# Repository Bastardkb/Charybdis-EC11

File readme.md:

# Charybdis EC11 PCB

EC11 PCB to be used in place of the trackball in the Charybdis keyboard.

`REV 1.2` is tested and working.

## EC11 Encoder
R1 and R2 pins are used for the encoder rotation pulses, these should be connected to unused pins on the microcontroller. The MOSI/MISO/SCLK/CS will be the most convenient - any two of these can be used.

For normal configuration of the pushbutton function with the Charybdis:
 - Bridge the 2 unmarked pads on the solder jumper
 - install a SOD-123 diode in the marked footprint
 - connect Col to a column and BTN to a row that corresponds with the missing thumb key matrix position

If your keyboard uses direct pin you will need to bridge the middle pad on the solder jumper with the marked pad. BTN should then be connected to a free GPIO pin on your microcontroller.

## LEDs
LEDs are optional. If not being used, VCC, GND, DIN, and DO can be ignored.

Otherwise:
- Install the capacitor and resistor on the marked footprints
- VCC and GND can be connected to wherever is the most convenient
- DIN and DO should be connected as part of the existing LED chain on the half - the suggested way to do this is to connect the DO from the PCB plate to the EC11 adapter DIN (instead of the thumb cluster), and the thumb cluster pcb DIN to the EC11 adapter DO

## Misc. Note
It should be possible to connect the adapter directly to the 6 pins of the trackball pin header on the shield for better aesthetics and modularity. However this would need custom matrix scanning code - to mix direct pin and switch matrix scanning, as well as a custom RGB LED driver to allow a second `RGB_DI` pin to be defined

## Parts you will need
### For every build

| Part name           | Amount | Format  |
| ------------------- | ------ | ------- |
| Diode, 1N4148       | 1      | SOD-123 |
| EC11 Rotary encoder | 1      |         |
| Rotary encoder PCB* | 1      |         |

*order the PCB using the latest *gerbers.zip from here: [Releases](https://github.com/Bastardkb/Charybdis-EC11/releases)

### Optional for LED functionality
| Part name        | Amount per board | Format | Value  |
| ---------------- | ---------------- | ------ | ------ |
| SK6812-MINI-E    | 12               |        |        |
| Capacitor        | 1                | 1206   | 1uF    |
| Resistor         | 1                | 1206   | 330ohm |

## Knob
The knob work on the 20mm tall and 6mm diameter knurled stem.

Licensed under CERN-OHL-W v2.

Copyright Quentin Lebastard 2022.

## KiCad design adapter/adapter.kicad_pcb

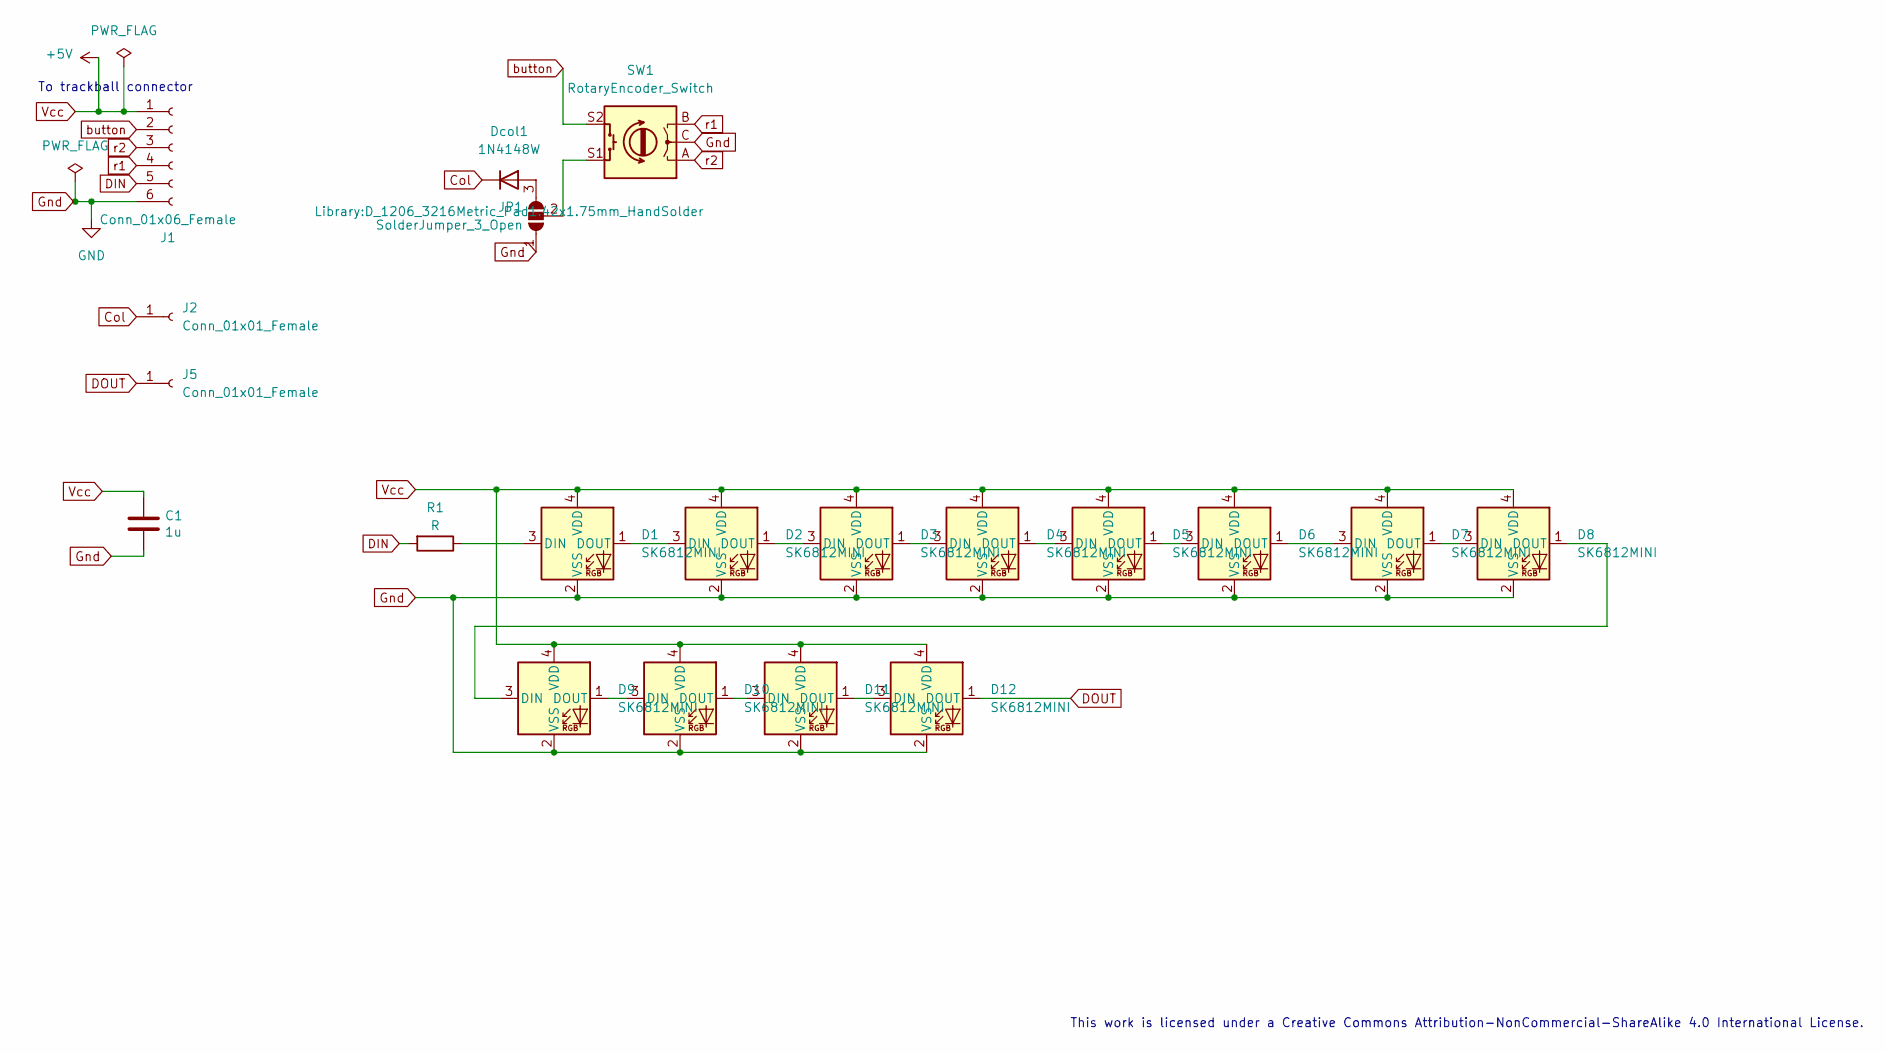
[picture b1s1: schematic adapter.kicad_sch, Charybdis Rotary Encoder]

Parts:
C1: 1u; C_1206_3216Metric_Pad1.33x1.80mm_HandSolder
D1, D2, D3, D4, D5, D6, D7, D8, D9, D10, D11, D12: SK6812MINI; YS-SK6812MINI-E
Dcol1: 1N4148W; D_1206_3216Metric_Pad1.42x1.75mm_HandSolder
J1: Conn_01x06_Female; 6_PinHeader
J2, J5: Conn_01x01_Female; 1_PinHeader
JP1: SolderJumper_3_Open; SolderJumper-3_P1.3mm_Open_RoundedPad1.0x1.5mm
R1: R; R_1206_3216Metric_Pad1.30x1.75mm_HandSolder
SW1: RotaryEncoder_Switch; RotaryEncoder_Alps_EC11E-Switch_Vertical_H20mm

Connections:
Col: Dcol1.1 (K), J2.1
DIN: J1.5, R1.2
DOUT: D12.1 (DOUT), J5.1
Gnd: C1.2, D1.2 (VSS), D2.2 (VSS), D3.2 (VSS), D4.2 (VSS), D5.2 (VSS), D6.2 (VSS), D7.2 (VSS), D8.2 (VSS), D9.2 (VSS), D10.2 (VSS), D11.2 (VSS), D12.2 (VSS), J1.6, JP1.1 (A), SW1.C
unnamed: D1.1 (DOUT), D2.3 (DIN)
unnamed: D1.3 (DIN), R1.1
unnamed: D2.1 (DOUT), D3.3 (DIN)
unnamed: D3.1 (DOUT), D4.3 (DIN)
unnamed: D4.1 (DOUT), D5.3 (DIN)
unnamed: D5.1 (DOUT), D6.3 (DIN)
unnamed: D6.1 (DOUT), D7.3 (DIN)
unnamed: D7.1 (DOUT), D8.3 (DIN)
unnamed: D8.1 (DOUT), D9.3 (DIN)
unnamed: D10.1 (DOUT), D11.3 (DIN)
unnamed: D9.1 (DOUT), D10.3 (DIN)
unnamed: D11.1 (DOUT), D12.3 (DIN)
unnamed: Dcol1.2 (A), JP1.3 (B)
unnamed: JP1.2 (C), SW1.S1
Vcc: C1.1, D1.4 (VDD), D2.4 (VDD), D3.4 (VDD), D4.4 (VDD), D5.4 (VDD), D6.4 (VDD), D7.4 (VDD), D8.4 (VDD), D9.4 (VDD), D10.4 (VDD), D11.4 (VDD), D12.4 (VDD), J1.1
button: J1.2, SW1.S2
r1: J1.4, SW1.B
r2: J1.3, SW1.A

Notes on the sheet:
To trackball connector
This work is licensed under a Creative Commons Attribution-NonCommercial-ShareAlike 4.0 International License.

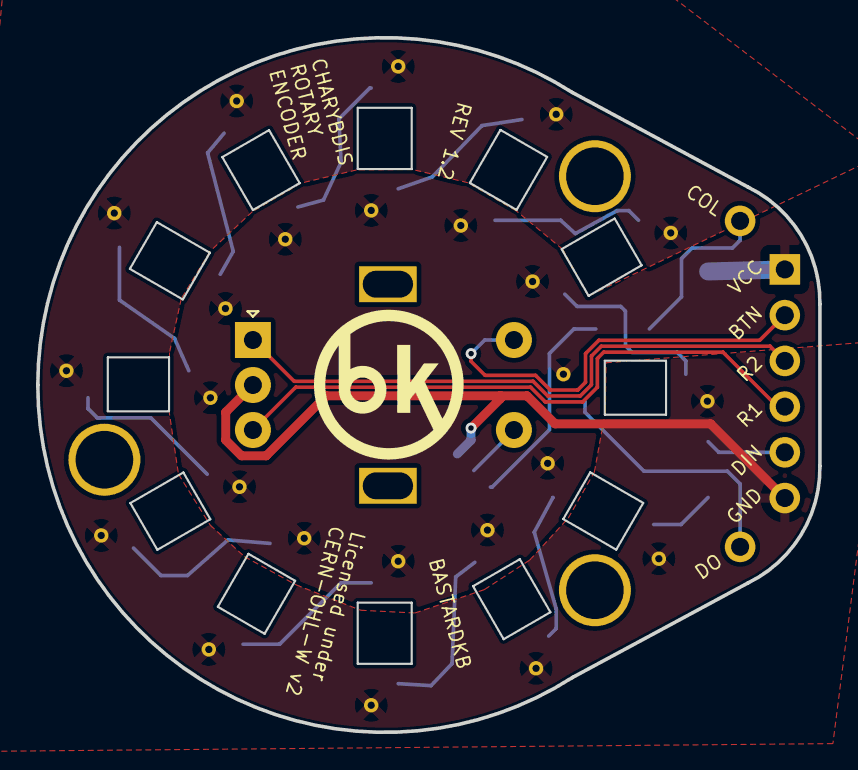
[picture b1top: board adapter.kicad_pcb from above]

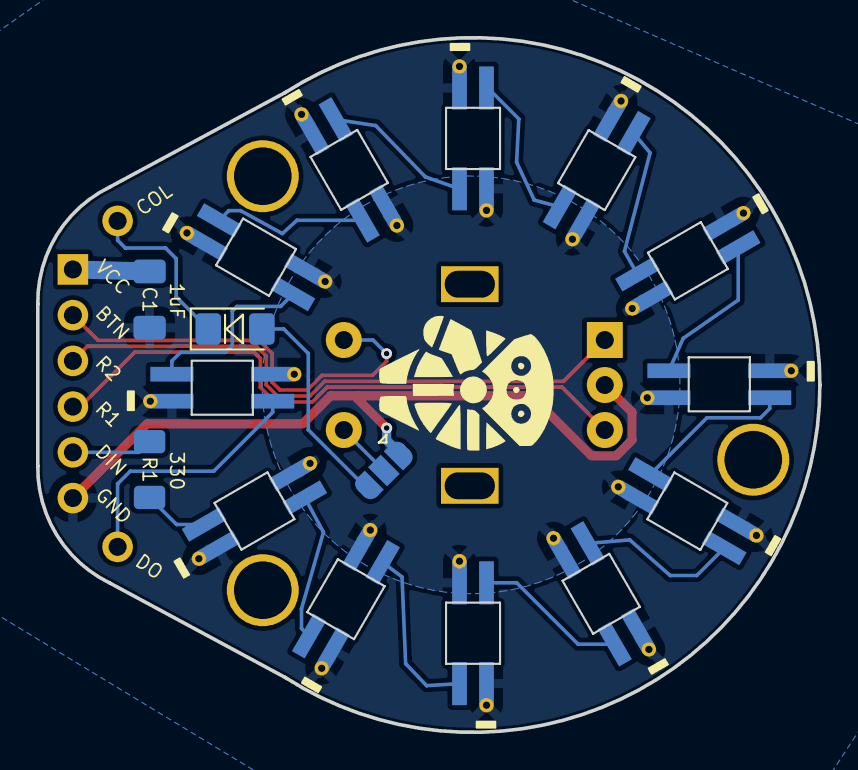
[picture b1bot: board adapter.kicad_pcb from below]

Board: 2 copper layers, 43.5 x 38.6 mm, 20 parts (16 on the bottom side), 22 nets.

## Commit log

2022-01-25 stuff
2022-01-26 routing
2022-01-26 routing, add R C
2022-01-26 logo
2022-01-26 logos
2022-01-26 license
2022-01-26 silkscreen
2022-01-28 add screw holes
2022-02-17 holes fix
2022-04-18 complete reroute
    - routing changed to fix din/dout paths
    - added dout header
    - renamed rgb header to din
    - moved SMT components to bottom side
    - changed silkscreen to rev 1.1
2022-04-18 complete reroute
2022-04-18 fixing drc flags
2022-04-18 fixing drc violations
2022-04-18 change vcc zone clearance
2022-04-18 images
2022-04-21 added row/col pin headers and jumpers for sw1 sw2
    Bodging the ec11 sw1 and sw2 pins to a free spot in the thumb cluster matrix would allow the pushbutton function to be mapped without needing a custom matrix.c code. Diode footprint added to support 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
    Jumpers added to allow selection between direct pin and matrix implementation
2022-04-21 update extra library footprints
2022-04-21 add mechanical files
2022-04-21 rearranged pins and reroute
    reverted BK logo to silkscreen
2022-04-25 flip LEDs to correct orientation
2022-04-25 added power flags to resolve erc error
2022-05-02 cleaned up extraneous gerber files that I accidentally added in a prior commit
2022-05-19 cleanup for 1.2 release
2022-05-19 tweaked image size on readme
2022-05-19 fix typo
2022-06-26 Angled bottom so knob is centered
2022-06-26 Added two knobs
2022-07-04 Removed large knob
2022-11-19 Adding materials to the readme, in shopping list form.
2022-11-19 fixing up url format
2022-12-29 move parts lists to tables
